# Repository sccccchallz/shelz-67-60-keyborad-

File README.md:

# shelz-67-60-keyborad-
This is a 67-key keyboard by shelz
(Still working on it)

The basic purpose is to reduce the way that the finger could access the backspace easier but keep the keycaps options same as the normal 64 keyboard.

My keyboard has a closer 1.25U backspace which is near to the key P , one function key (fn2) is set on the left of the backspace key that has not input without other keys together  or lock to another layout such as coleman layout by press the function 1 key together. Therefore, the place of original 2U backspace became "[" and "]".
(you could defintely switch to the defualt 64 layout with double 1U backspace and 1U'[', 1.25'U'] and the 1.25U'\')

Well, I am a brake spacebar lover lol.
And due to my IME useed to typing chinese does not require the numbers to choose characters, I was trying to design the 40%, however, my mommy and daddy are still using the traditional IME，I switched to 60%, If you are from the English speaking contry, you could just delete the first row and switch tab to esc, the tab could use the fn2 to type in, this is why I put the fn2 to the left of the backspace, one is to reduce the typo on the backspace, one is for the easier access to the function key.

Here is my special layout.

the json file for the lceda is in the folder. If you are from China and using the lceda(立创)　you could use dah.

Thanks the KLE and KFB for helping me design my own layout more easily.

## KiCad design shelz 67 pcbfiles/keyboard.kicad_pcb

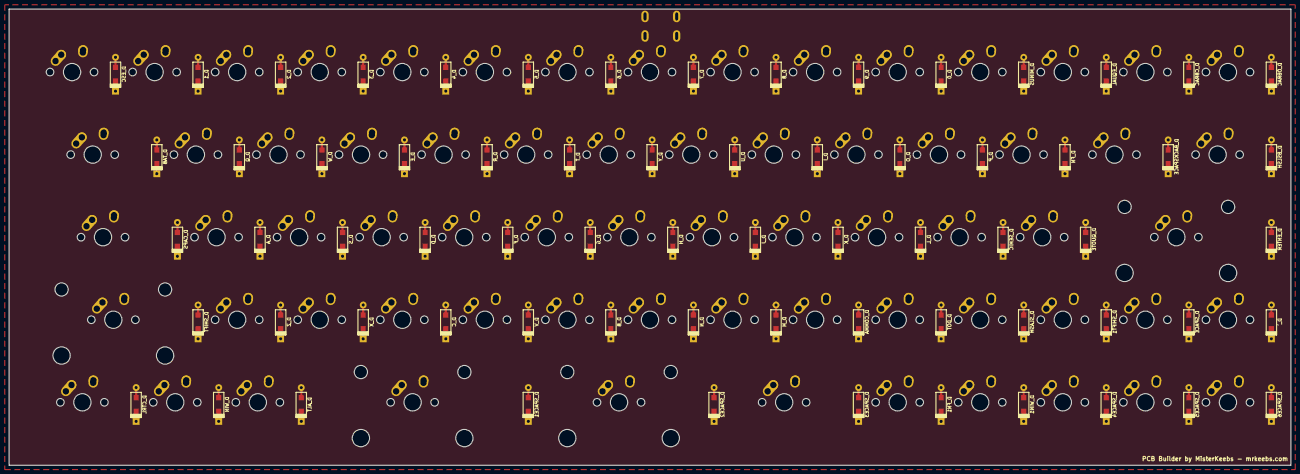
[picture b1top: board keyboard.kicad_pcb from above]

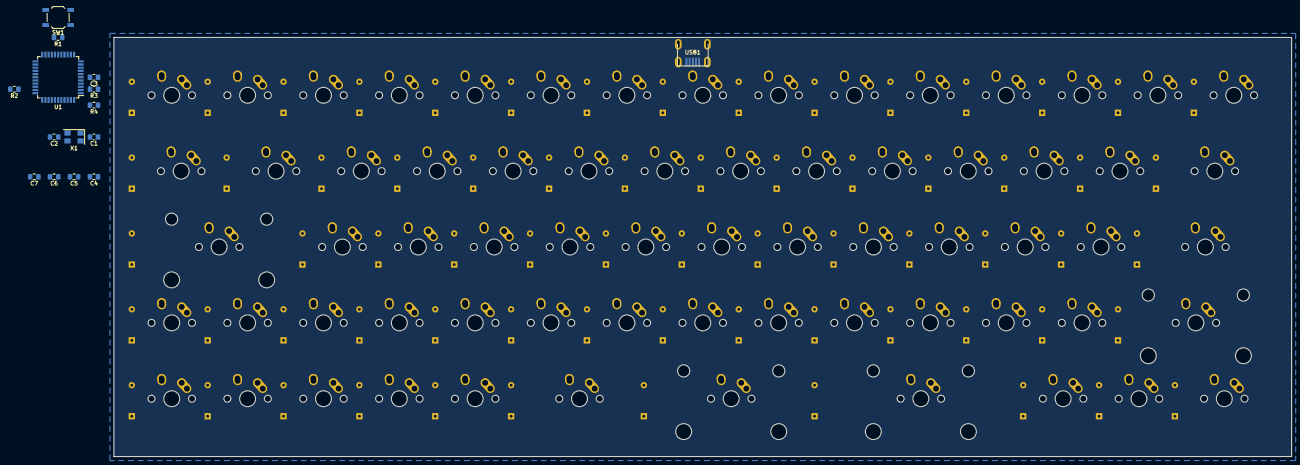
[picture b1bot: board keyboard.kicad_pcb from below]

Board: 2 copper layers, 295.8 x 105.2 mm, 149 parts (15 on the bottom side), 98 nets, no tracks yet.

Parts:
C1, C2, C3, C4, C5, C6, C7: 22pF; C_0805_2012Metric_Pad1.15x1.40mm_HandSolder
D_0, D_1, D_2, D_3, D_4, D_5, D_6, D_7, D_8, D_9: D; D_SOD123_axial
D_A: D; D_SOD123_axial
D_ALT: D; D_SOD123_axial
D_B: D; D_SOD123_axial
D_BACKSPACE: D; D_SOD123_axial
D_BSLSH: D; D_SOD123_axial
D_C: D; D_SOD123_axial
D_CAPS: D; D_SOD123_axial
D_CBRAC: D; D_SOD123_axial
D_COMMA: D; D_SOD123_axial
D_CTRL: D; D_SOD123_axial
D_D: D; D_SOD123_axial
D_DOT: D; D_SOD123_axial
D_E: D; D_SOD123_axial
D_ENTER: D; D_SOD123_axial
D_EQUAL: D; D_SOD123_axial
D_ESC: D; D_SOD123_axial
D_F: D; D_SOD123_axial
D_FN, D_FN1: D; D_SOD123_axial
D_G: D; D_SOD123_axial
D_H: D; D_SOD123_axial
D_I: D; D_SOD123_axial
D_J: D; D_SOD123_axial
D_K: D; D_SOD123_axial
D_L: D; D_SOD123_axial
D_M: D; D_SOD123_axial
D_MINUS: D; D_SOD123_axial
D_N: D; D_SOD123_axial
D_O: D; D_SOD123_axial
D_OBRAC: D; D_SOD123_axial
D_P: D; D_SOD123_axial
D_Q: D; D_SOD123_axial
D_QUOTE: D; D_SOD123_axial
D_R: D; D_SOD123_axial
D_S: D; D_SOD123_axial
D_SEMIC: D; D_SOD123_axial
D_SHIFT, D_SHIFT1: D; D_SOD123_axial
D_SLASH: D; D_SOD123_axial
D_SPACE, D_SPACE1, D_SPACE2, D_SPACE3, D_SPACE4, D_SPACE5, D_SPACE6: D; D_SOD123_axial
D_T: D; D_SOD123_axial
D_TAB: D; D_SOD123_axial
D_U: D; D_SOD123_axial
D_V: D; D_SOD123_axial
D_W: D; D_SOD123_axial
D_WIN, D_WIN1: D; D_SOD123_axial
D_X: D; D_SOD123_axial
D_Y: D; D_SOD123_axial
D_Z: D; D_SOD123_axial
D_`: D; D_SOD123_axial
K_0, K_1, K_2, K_3, K_4, K_5, K_6, K_7, K_8, K_9: KEYSW; MX-1U-NoLED
K_A: KEYSW; MX-1U-NoLED
K_ALT: KEYSW; MX-1U-NoLED
K_B: KEYSW; MX-1U-NoLED
K_BACKSPACE: KEYSW; MX-1.25U-NoLED
K_BSLSH: KEYSW; MX-1.25U-NoLED
K_C: KEYSW; MX-1U-NoLED
K_CAPS: KEYSW; MX-1.75U-NoLED
K_CBRAC: KEYSW; MX-1U-NoLED
K_COMMA: KEYSW; MX-1U-NoLED
K_CTRL: KEYSW; MX-1.25U-NoLED
K_D: KEYSW; MX-1U-NoLED
K_DOT: KEYSW; MX-1U-NoLED
K_E: KEYSW; MX-1U-NoLED
K_ENTER: KEYSW; MX-2.25U-NoLED
K_EQUAL: KEYSW; MX-1U-NoLED
K_ESC: KEYSW; MX-1U-NoLED
K_F: KEYSW; MX-1U-NoLED
K_FN, K_FN1: KEYSW; MX-1U-NoLED
K_G: KEYSW; MX-1U-NoLED
K_H: KEYSW; MX-1U-NoLED
K_I: KEYSW; MX-1U-NoLED
K_J: KEYSW; MX-1U-NoLED
K_K: KEYSW; MX-1U-NoLED
K_L: KEYSW; MX-1U-NoLED
K_M: KEYSW; MX-1U-NoLED
K_MINUS: KEYSW; MX-1U-NoLED
K_N: KEYSW; MX-1U-NoLED
K_O: KEYSW; MX-1U-NoLED
K_OBRAC: KEYSW; MX-1U-NoLED
K_P: KEYSW; MX-1U-NoLED
K_Q: KEYSW; MX-1U-NoLED
K_QUOTE: KEYSW; MX-1U-NoLED
K_R: KEYSW; MX-1U-NoLED
K_S: KEYSW; MX-1U-NoLED
K_SEMIC: KEYSW; MX-1U-NoLED
K_SHIFT: KEYSW; MX-2U-NoLED
K_SHIFT1: KEYSW; MX-1U-NoLED
K_SLASH: KEYSW; MX-1U-NoLED
K_SPACE, K_SPACE4, K_SPACE5, K_SPACE6: KEYSW; MX-1U-NoLED
K_SPACE1: KEYSW; MX-2.75U-NoLED
K_SPACE2: KEYSW; MX-2.25U-NoLED
K_SPACE3: KEYSW; MX-1.75U-NoLED
K_T: KEYSW; MX-1U-NoLED
K_TAB: KEYSW; MX-1.5U-NoLED
K_U: KEYSW; MX-1U-NoLED
K_V: KEYSW; MX-1U-NoLED
K_W: KEYSW; MX-1U-NoLED
K_WIN, K_WIN1: KEYSW; MX-1U-NoLED
K_X: KEYSW; MX-1U-NoLED
K_Y: KEYSW; MX-1U-NoLED
K_Z: KEYSW; MX-1U-NoLED
K_`: KEYSW; MX-1U-NoLED
R1, R2: 10k; R_0805_2012Metric_Pad1.15x1.40mm_HandSolder
R3, R4: 22; R_0805_2012Metric_Pad1.15x1.40mm_HandSolder
SW1: SW_PUSH; SW_SPST_TL3342
U1: ATMEGA32U4; TQFP-44_10x10mm_P0.8mm
USB1: Molex-0548190589; Molex-0548190589-Assembly
X1: XTAL_GND; Crystal_SMD_5032-4Pin_5.0x3.2mm

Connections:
/col0: K_CAPS.1, K_CTRL.1, K_ESC.1, K_SHIFT.1, K_TAB.1, U1.29
/col1: K_1.1, K_A.1, K_Q.1, K_WIN.1, K_Z.1, U1.30
/col2: K_2.1, K_ALT.1, K_S.1, K_W.1, K_X.1, U1.12
/col3: K_3.1, K_C.1, K_D.1, K_E.1, K_SPACE1.1, U1.31
/col4: K_4.1, K_F.1, K_R.1, K_V.1, U1.32
/col5: K_5.1, K_B.1, K_G.1, K_SPACE2.1, K_T.1, U1.18
/col6: K_6.1, K_H.1, K_N.1, K_Y.1, U1.19
/col7: K_7.1, K_J.1, K_M.1, K_SPACE3.1, K_U.1, U1.20
/col8: K_8.1, K_COMMA.1, K_I.1, K_K.1, U1.21
/col9: K_9.1, K_DOT.1, K_FN1.1, K_L.1, K_O.1, U1.25
/col10: K_0.1, K_P.1, K_SEMIC.1, K_SLASH.1, K_WIN1.1, U1.22
/col11: K_FN.1, K_MINUS.1, K_QUOTE.1, K_SHIFT1.1, K_SPACE4.1, U1.26
/col12: K_BACKSPACE.1, K_ENTER.1, K_EQUAL.1, K_SPACE.1, K_SPACE5.1, U1.27
/col13: K_BSLSH.1, K_CBRAC.1, K_SPACE6.1, K_`.1, U1.41
/col14: K_OBRAC.1, U1.40
/row0: D_0.1, D_1.1, D_2.1, D_3.1, D_4.1, D_5.1, D_6.1, D_7.1, D_8.1, D_9.1, D_CBRAC.1, D_EQUAL.1, D_ESC.1, D_MINUS.1, D_OBRAC.1, U1.8
/row1: D_BACKSPACE.1, D_BSLSH.1, D_E.1, D_FN.1, D_I.1, D_O.1, D_P.1, D_Q.1, D_R.1, D_T.1, D_TAB.1, D_U.1, D_W.1, D_Y.1, U1.9
/row2: D_A.1, D_CAPS.1, D_D.1, D_ENTER.1, D_F.1, D_G.1, D_H.1, D_J.1, D_K.1, D_L.1, D_QUOTE.1, D_S.1, D_SEMIC.1, U1.10
/row3: D_B.1, D_C.1, D_COMMA.1, D_DOT.1, D_M.1, D_N.1, D_SHIFT.1, D_SHIFT1.1, D_SLASH.1, D_SPACE.1, D_V.1, D_X.1, D_Z.1, D_`.1, U1.11
/row4: D_ALT.1, D_CTRL.1, D_FN1.1, D_SPACE1.1, D_SPACE2.1, D_SPACE3.1, D_SPACE4.1, D_SPACE5.1, D_SPACE6.1, D_WIN.1, D_WIN1.1, U1.28
GND: C1.2, C2.2, C3.2, C4.2, C5.2, C6.2, C7.2, R2.2, SW1.1, U1.5, U1.15, U1.23, USB1.1, X1.2, X1.4
unnamed: C1.1, U1.16, X1.1
unnamed: C2.1, U1.17, X1.3
unnamed: C3.1, U1.6
unnamed: D_0.2, K_0.2
unnamed: D_1.2, K_1.2
unnamed: D_2.2, K_2.2
unnamed: D_3.2, K_3.2
unnamed: D_4.2, K_4.2
unnamed: D_5.2, K_5.2
unnamed: D_6.2, K_6.2
unnamed: D_7.2, K_7.2
unnamed: D_8.2, K_8.2
unnamed: D_9.2, K_9.2
unnamed: D_A.2, K_A.2
unnamed: D_ALT.2, K_ALT.2
unnamed: D_B.2, K_B.2
unnamed: D_BACKSPACE.2, K_BACKSPACE.2
unnamed: D_BSLSH.2, K_BSLSH.2
unnamed: D_C.2, K_C.2
unnamed: D_CAPS.2, K_CAPS.2
unnamed: D_CBRAC.2, K_CBRAC.2
unnamed: D_COMMA.2, K_COMMA.2
unnamed: D_CTRL.2, K_CTRL.2
unnamed: D_D.2, K_D.2
unnamed: D_DOT.2, K_DOT.2
unnamed: D_E.2, K_E.2
unnamed: D_ENTER.2, K_ENTER.2
unnamed: D_EQUAL.2, K_EQUAL.2
unnamed: D_ESC.2, K_ESC.2
unnamed: D_F.2, K_F.2
unnamed: D_FN1.2, K_FN1.2
unnamed: D_FN.2, K_FN.2
unnamed: D_G.2, K_G.2
unnamed: D_H.2, K_H.2
unnamed: D_I.2, K_I.2
unnamed: D_J.2, K_J.2
unnamed: D_K.2, K_K.2
unnamed: D_L.2, K_L.2
unnamed: D_M.2, K_M.2
unnamed: D_MINUS.2, K_MINUS.2
unnamed: D_N.2, K_N.2
unnamed: D_O.2, K_O.2
unnamed: D_OBRAC.2, K_OBRAC.2
unnamed: D_P.2, K_P.2
unnamed: D_Q.2, K_Q.2
unnamed: D_QUOTE.2, K_QUOTE.2
unnamed: D_R.2, K_R.2
unnamed: D_S.2, K_S.2
unnamed: D_SEMIC.2, K_SEMIC.2
unnamed: D_SHIFT1.2, K_SHIFT1.2
unnamed: D_SHIFT.2, K_SHIFT.2
unnamed: D_SLASH.2, K_SLASH.2
unnamed: D_SPACE1.2, K_SPACE1.2
unnamed: D_SPACE2.2, K_SPACE2.2
unnamed: D_SPACE3.2, K_SPACE3.2
unnamed: D_SPACE4.2, K_SPACE4.2
unnamed: D_SPACE5.2, K_SPACE5.2
unnamed: D_SPACE6.2, K_SPACE6.2
unnamed: D_SPACE.2, K_SPACE.2
unnamed: D_T.2, K_T.2
unnamed: D_TAB.2, K_TAB.2
unnamed: D_U.2, K_U.2
unnamed: D_V.2, K_V.2
unnamed: D_W.2, K_W.2
unnamed: D_WIN1.2, K_WIN1.2
unnamed: D_WIN.2, K_WIN.2
unnamed: D_X.2, K_X.2
unnamed: D_Y.2, K_Y.2
unnamed: D_Z.2, K_Z.2
unnamed: D_`.2, K_`.2
unnamed: R1.1, SW1.2, U1.13
unnamed: R2.1, U1.33
unnamed: R3.1, U1.3
unnamed: R4.1, U1.4
unnamed: R3.2, USB1.2
unnamed: R4.2, USB1.3
VCC: C4.1, C5.1, C6.1, C7.1, R1.2, U1.2, U1.14, U1.24, USB1.5

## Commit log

2021-03-31 pcbs
